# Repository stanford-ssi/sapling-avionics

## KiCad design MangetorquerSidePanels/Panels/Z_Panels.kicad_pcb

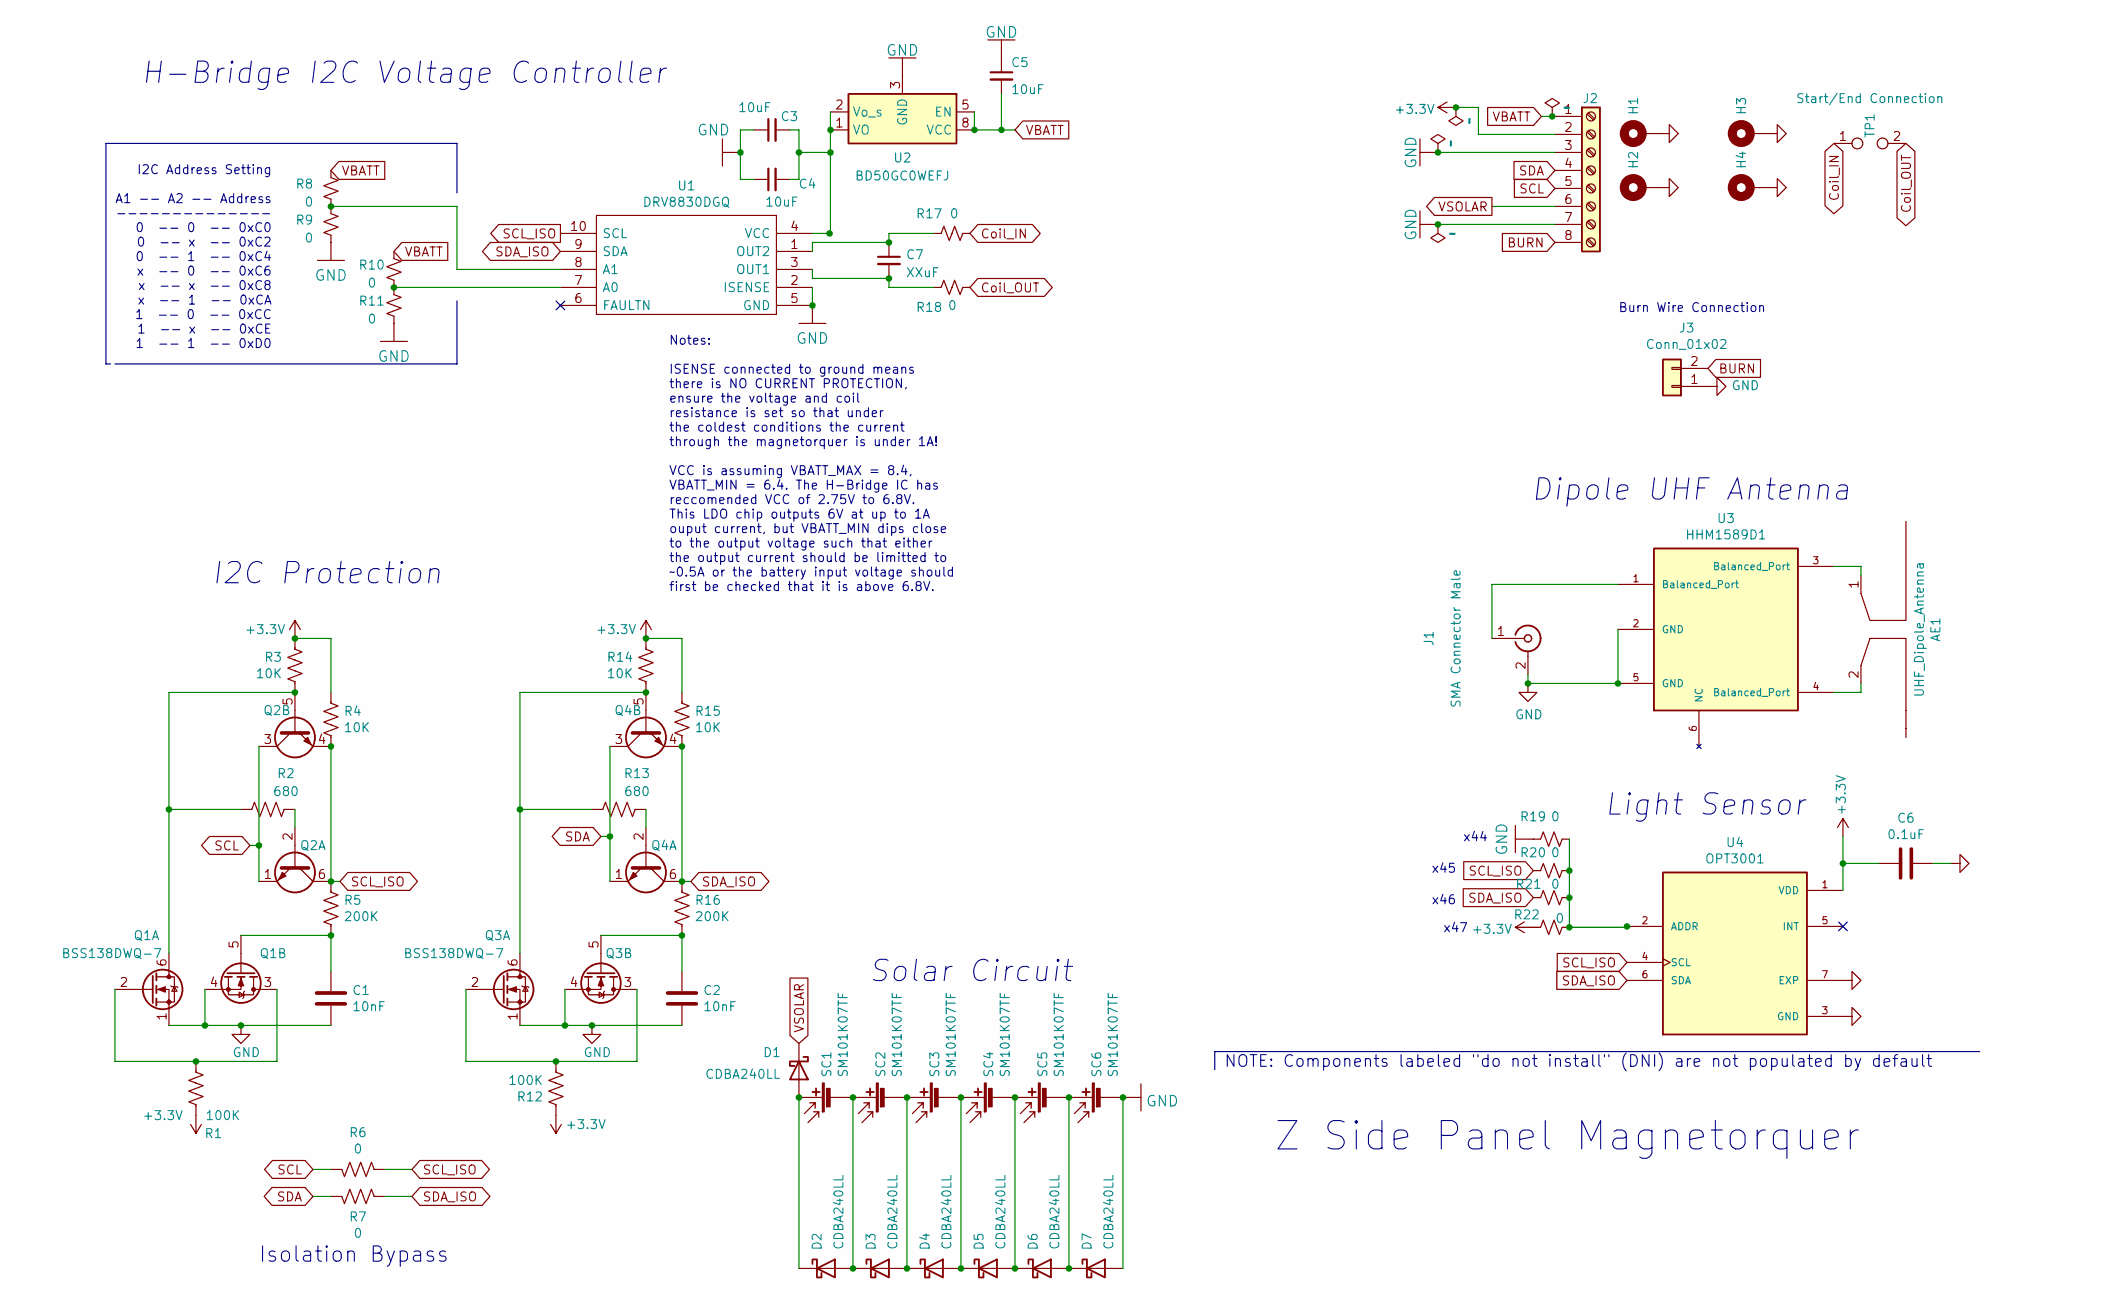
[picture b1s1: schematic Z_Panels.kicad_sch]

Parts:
AE1: UHF_Dipole_Antenna; UHF_Dipole_Antenna_Mount
C1, C2: 10nF; C_0603_1608Metric
C3, C4, C5: 10uF; C_1206_3216Metric
C6: 0.1uF; C_0603_1608Metric
C7: XXuF; C_1210_3225Metric
D1, D2, D3, D4, D5, D6, D7: CDBA240LL; DO-214AC
H1, H2, H3, H4: MountingHole_2.2mm_M2_DIN965_Pad_TopBottom
J1: SMA Connector Male; SMA_Amphenol_901-144_Vertical
J2: Screw_Terminal_01x08; PinHeader_1x08_P2.54mm_Vertical
J3: Conn_01x02; Burn_Wire_Connection
Q1, Q3: BSS138DWQ-7; Manufacturer_Part_Number BSS138DWQ-7; Mouser Part Number 621-BSS138DWQ-7
Q2, Q4: MBT2222ADW1T1; SOT-363_SC-70-6
R1, R12: 100K; R_0603_1608Metric
R2, R13: 680; R_0603_1608Metric
R3, R4, R14, R15: 10K; R_0603_1608Metric
R5, R16: 200K; R_0603_1608Metric
R6, R7, R8, R9, R10, R11, R17, R18, R19, R20, R21, R22: 0; R_0603_1608Metric
SC1, SC2, SC3, SC4, SC5, SC6: SM101K07TF
TP1: Start/End Connection; TestPointConnection
U1: DRV8830DGQ; Manufacturer_Part_Number DRV8830DGQR; Mouser Part Number 595-DRV8830DGQR
U2: BD50GC0WEFJ; HTSOP-8-1EP_3.9x4.9mm_P1.27mm_EP2.4x3.2mm
U3: HHM1589D1; Balun_Johanson_5400BL15B050E
U4: OPT3001

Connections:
+3V3: C6.1, J2.2, R1.2, R3.1, R4.2, R12.2, R14.1, R15.2, R22.1, U4.1 (VDD)
BURN: J2.8, J3.2
Coil_IN: R17.2, TP1.1
Coil_OUT: R18.2, TP1.2
unnamed: AE1.1, U3.3 (Balanced_Port)
unnamed: AE1.2, U3.4 (Balanced_Port)
unnamed: C3.2, C4.2, U1.4 (VCC), U2.1 (VO), U2.2 (Vo_s)
unnamed: D1.2 (A), D2.1 (K), SC1.1 (+)
unnamed: D2.2 (A), D3.1 (K), SC1.2 (-), SC2.1 (+)
unnamed: D3.2 (A), D4.1 (K), SC2.2 (-), SC3.1 (+)
unnamed: D4.2 (A), D5.1 (K), SC3.2 (-), SC4.1 (+)
unnamed: D5.2 (A), D6.1 (K), SC4.2 (-), SC5.1 (+)
unnamed: D6.2 (A), D7.1 (K), SC5.2 (-), SC6.1 (+)
unnamed: J1.1 (In), U3.1 (Balanced_Port)
unnamed: Q2.2 (B1), R2.2
unnamed: Q3.2 (G2), Q3.3 (D2), R12.1
unnamed: Q4.2 (B1), R13.1
unnamed: Q1.2 (G2), Q1.3 (D2), R1.1
unnamed: Q1.6 (D1), Q2.5 (B2), R2.1, R3.2
unnamed: C1.1, Q1.5 (G1), R5.1
unnamed: R8.2, R9.1, U1.8 (A1)
unnamed: R10.2, R11.1, U1.7 (A0)
unnamed: Q3.6 (D1), Q4.5 (B2), R13.2, R14.2
unnamed: C2.1, Q3.5 (G1), R16.1
unnamed: C7.1, R17.1, U1.1 (OUT2)
unnamed: C7.2, R18.1, U1.3 (OUT1)
unnamed: R19.2, R20.2, R21.2, R22.2, U4.2 (ADDR)
SCL: J2.5, Q2.1 (E1), Q2.3 (C2), R6.1
SCL_ISO: Q2.4 (E2), Q2.6 (C1), R4.1, R5.2, R6.2, R20.1, U1.10 (SCL), U4.4 (SCL)
SDA: J2.4, Q4.1 (E1), Q4.3 (C2), R7.1
SDA_ISO: Q4.4 (E2), Q4.6 (C1), R7.2, R15.1, R16.2, R21.1, U1.9 (SDA), U4.6 (SDA)
VBATT: C5.2, J2.1, R8.1, R10.1, U2.5 (EN), U2.8 (VCC)
VSOLAR: D1.1 (K), J2.6

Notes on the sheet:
Notes: ISENSE connected to ground means there is NO CURRENT PROTECTION, ensure the voltage and coil resistance is set so that under the coldest conditions the current through the magnetorquer is under 1A! VCC is assuming VBATT_MAX = 8.4, VBATT_MIN = 6.4. The H-Bridge IC has reccomended VCC of 2.75V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
x47
NOTE: Components labeled "do not install" (DNI) are not populated by default
Solar Circuit
x45
Z Side Panel Magnetorquer
Light Sensor
I2C Address Setting A1 -- A2 -- Address -------------- 0 -- 0 -- 0xC0 0 -- x -- 0xC2 0 -- 1 -- 0xC4 x -- 0 -- 0xC6 x -- x -- 0xC8 x -- 1 -- 0xCA 1 -- 0 -- 0xCC 1 -- x -- 0xCE 1 -- 1 -- 0xD0
H-Bridge I2C Voltage Controller
Burn Wire Connection
Dipole UHF Antenna
x44
Isolation Bypass
x46
I2C Protection

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
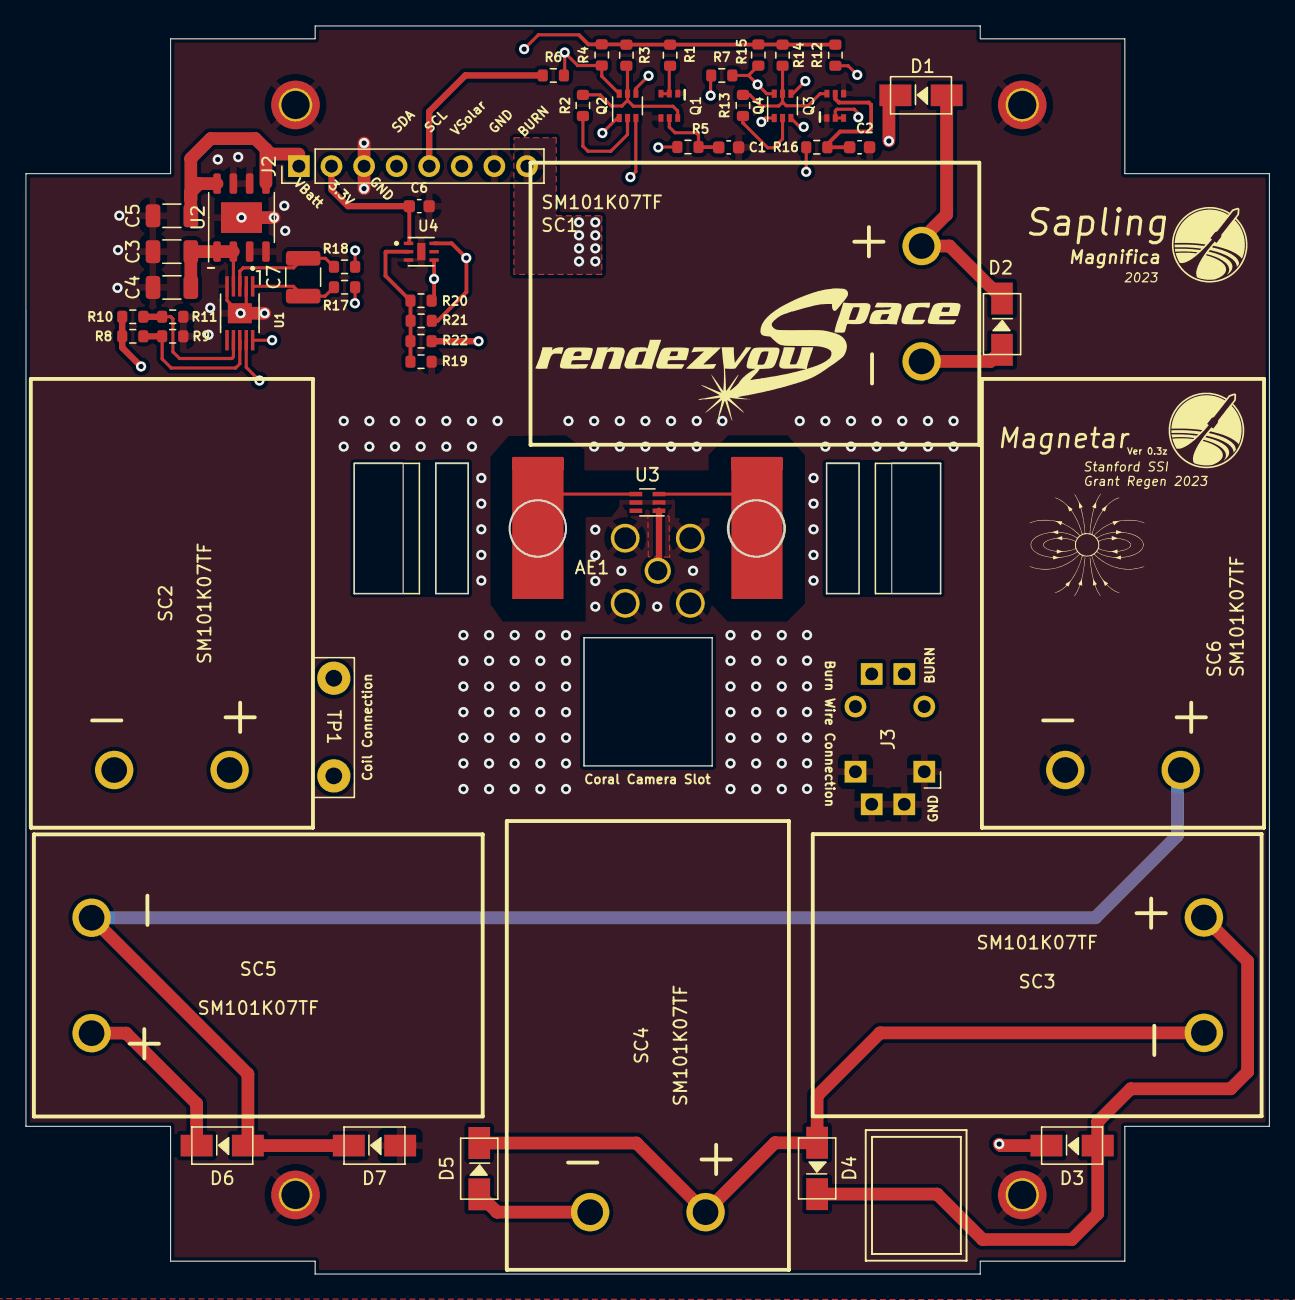
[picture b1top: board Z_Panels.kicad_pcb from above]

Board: 6 copper layers, 97.0 x 97.3 mm, 59 parts (1 on the bottom side), 34 nets.

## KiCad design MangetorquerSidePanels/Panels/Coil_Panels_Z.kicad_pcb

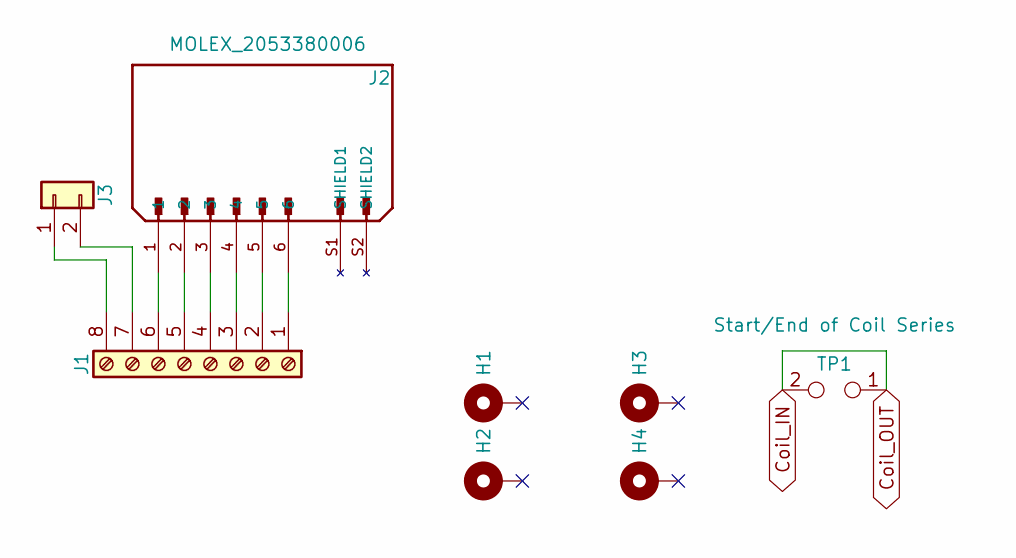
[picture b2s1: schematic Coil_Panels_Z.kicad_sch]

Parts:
H1, H2, H3, H4: MountingHole_2.2mm_M2_DIN965_Pad_TopBottom
J1: Screw_Terminal_01x08; PinHeader_1x08_P2.54mm_Vertical
J2: MOLEX_2053380006
J3: Conn_01x02; 2053380002
TP1: Start/End of Coil Series; TestPointConnection

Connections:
Coil_IN: TP1.1, TP1.2
unnamed: J1.7, J3.2
unnamed: J1.6, J2.1
unnamed: J1.5, J2.2
unnamed: J1.4, J2.3
unnamed: J1.3, J2.4
unnamed: J1.2, J2.5
unnamed: J1.1, J2.6
unnamed: J1.8, J3.1

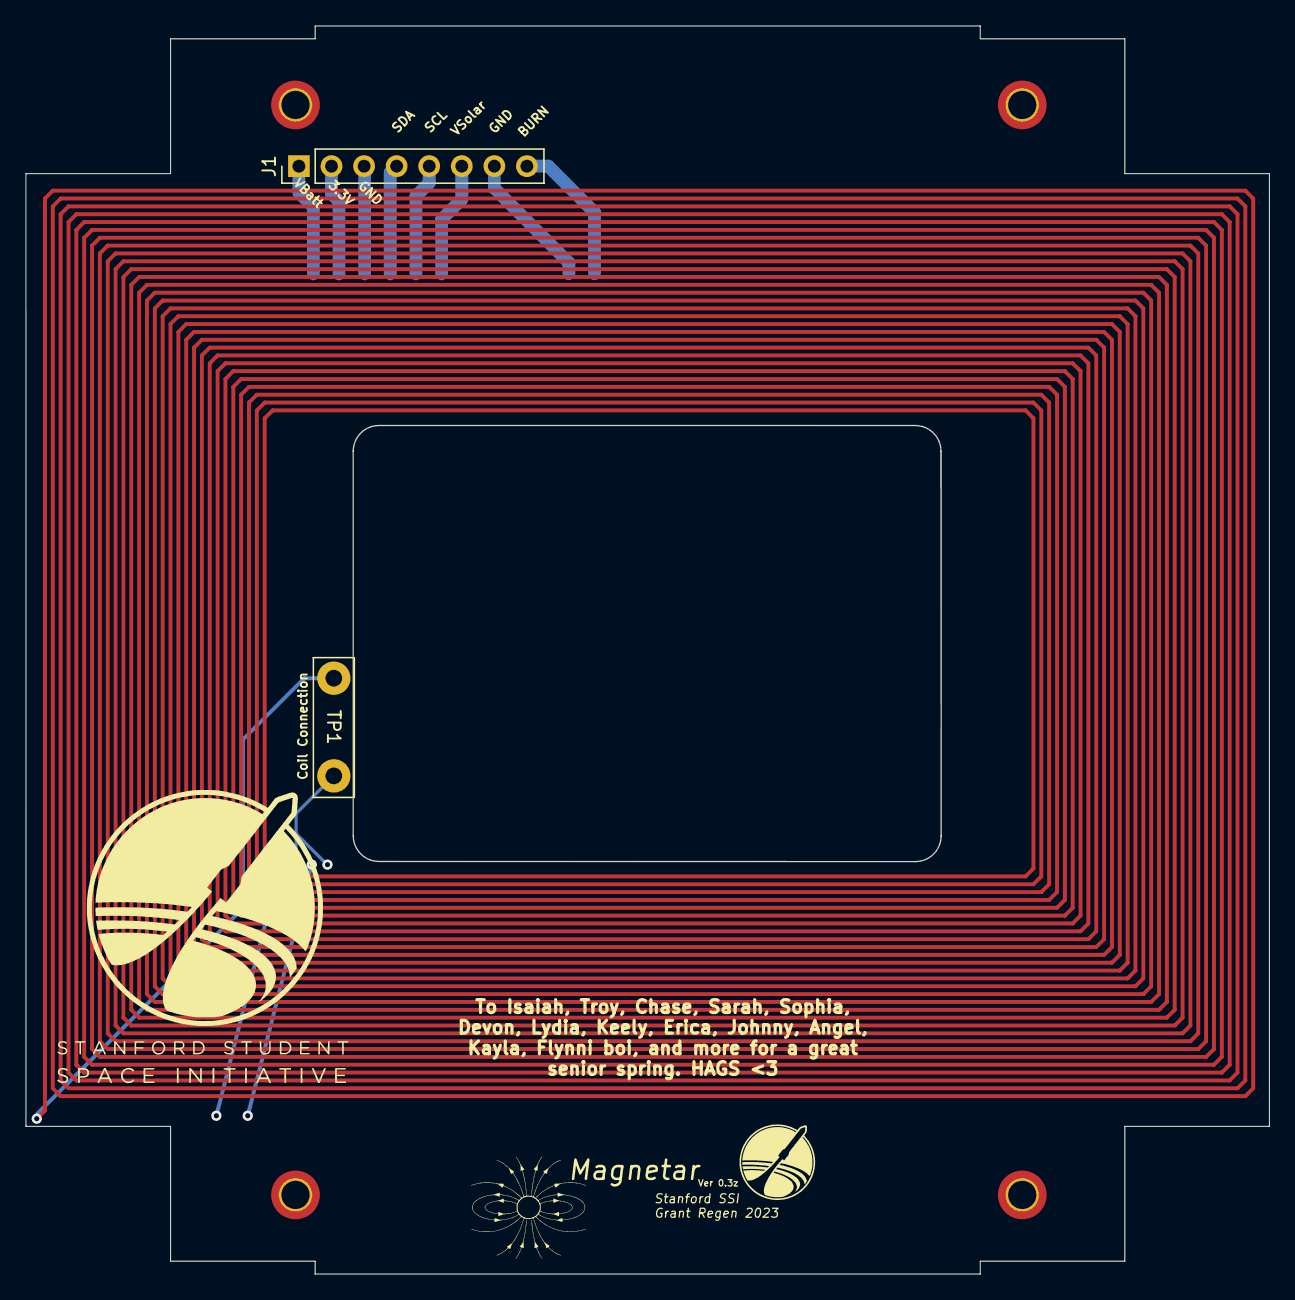
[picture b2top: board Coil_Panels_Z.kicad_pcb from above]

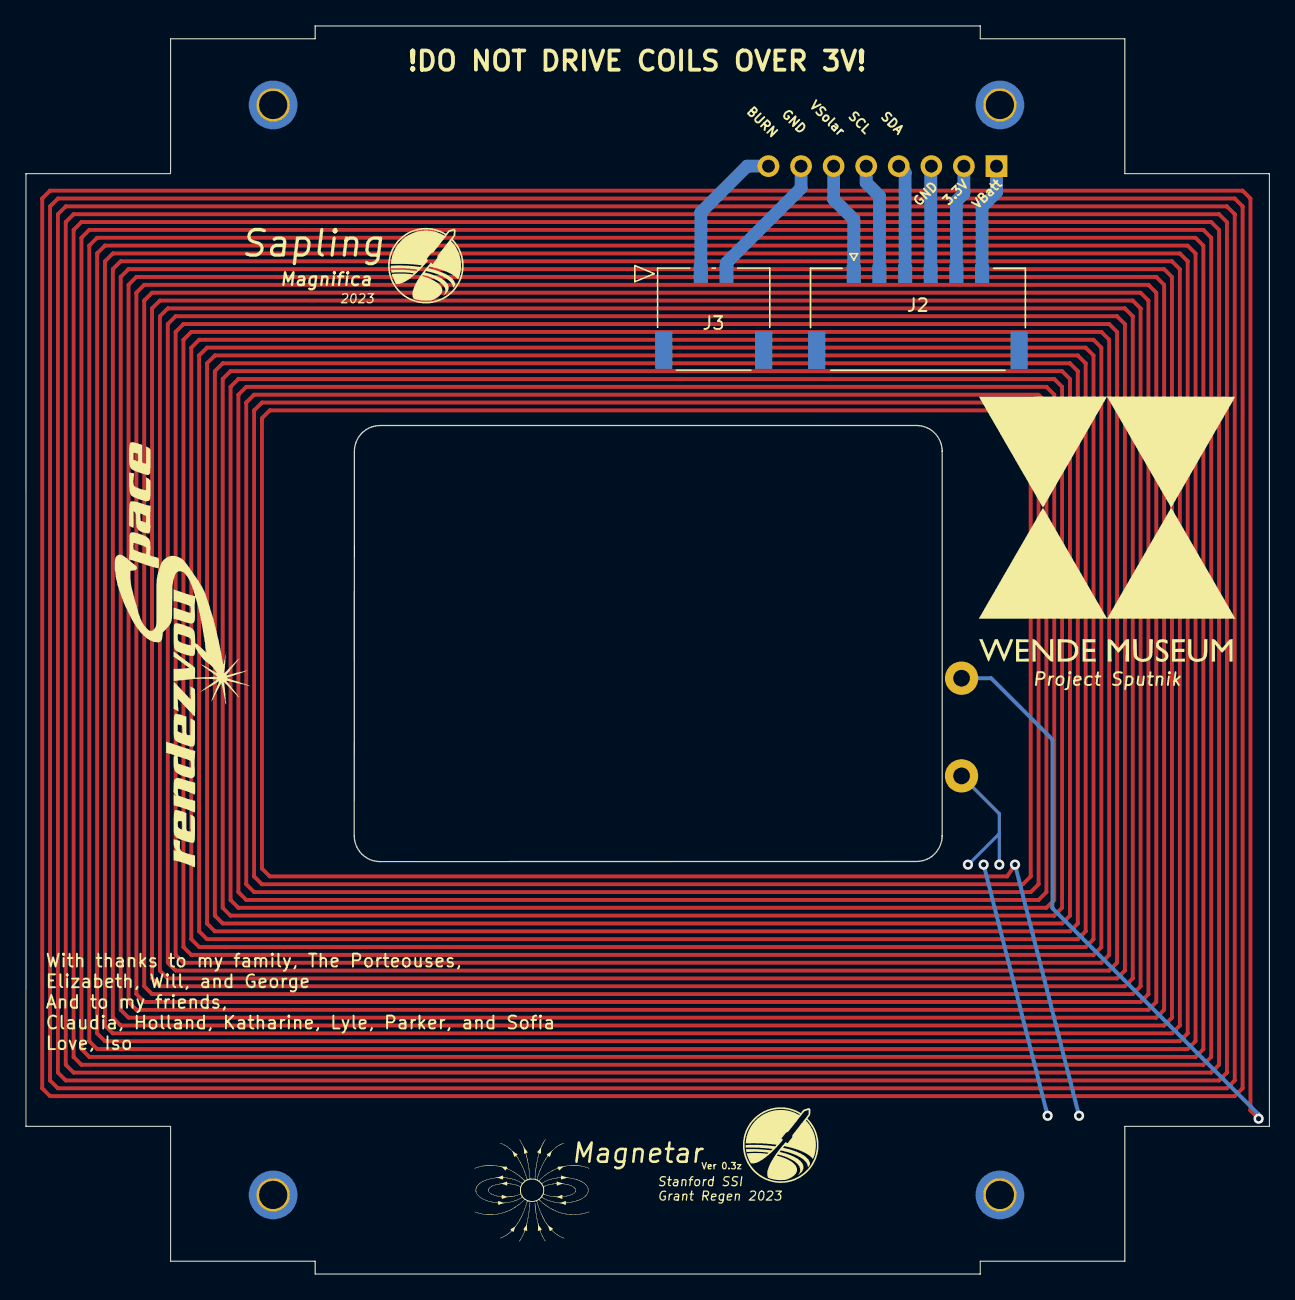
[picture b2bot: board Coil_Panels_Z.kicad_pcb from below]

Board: 6 copper layers, 97.0 x 97.3 mm, 8 parts (2 on the bottom side), 9 nets.

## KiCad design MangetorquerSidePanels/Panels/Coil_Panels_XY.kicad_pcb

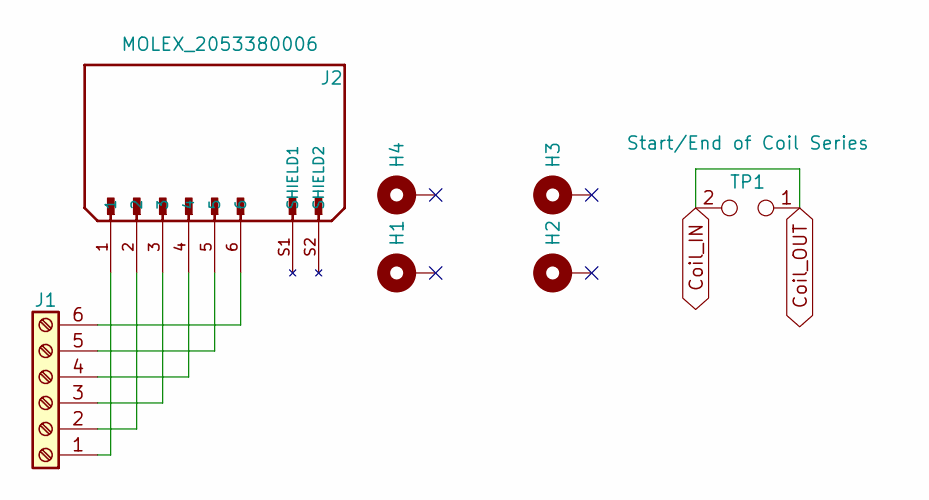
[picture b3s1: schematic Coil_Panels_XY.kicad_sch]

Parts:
H1, H2, H3, H4: MountingHole_2.2mm_M2_DIN965_Pad_TopBottom
J1: Through_Hole_1; PinHeader_1x06_P2.54mm_Vertical
J2: MOLEX_2053380006
TP1: Start/End of Coil Series; TestPointConnection

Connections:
Coil_IN: TP1.1, TP1.2
unnamed: J1.1, J2.1
unnamed: J1.2, J2.2
unnamed: J1.3, J2.3
unnamed: J1.4, J2.4
unnamed: J1.5, J2.5
unnamed: J1.6, J2.6

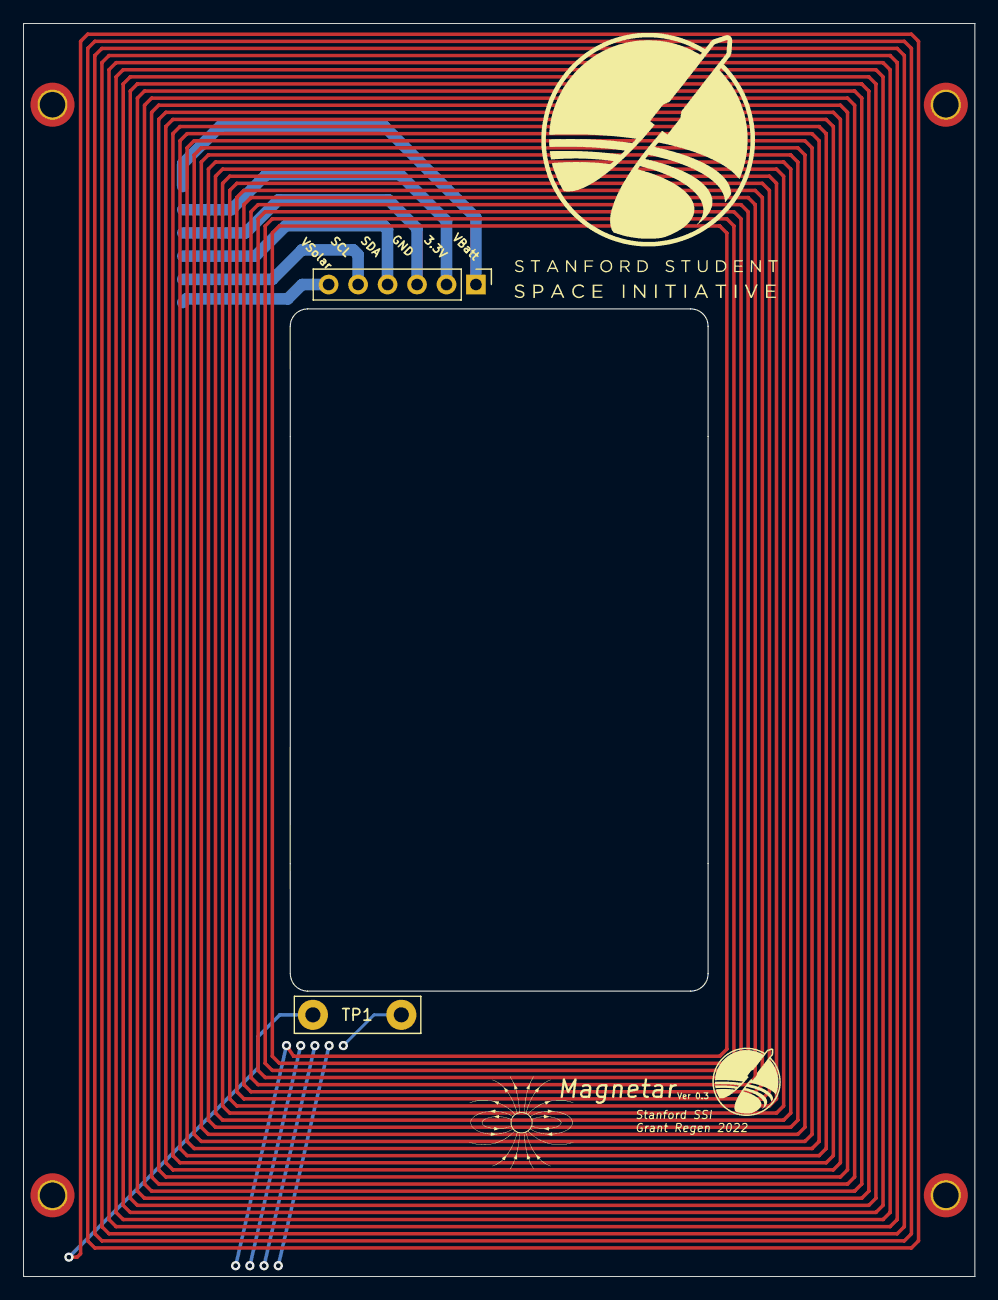
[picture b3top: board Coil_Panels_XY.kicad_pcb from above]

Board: 6 copper layers, 82.0 x 108.0 mm, 7 parts (1 on the bottom side), 7 nets.

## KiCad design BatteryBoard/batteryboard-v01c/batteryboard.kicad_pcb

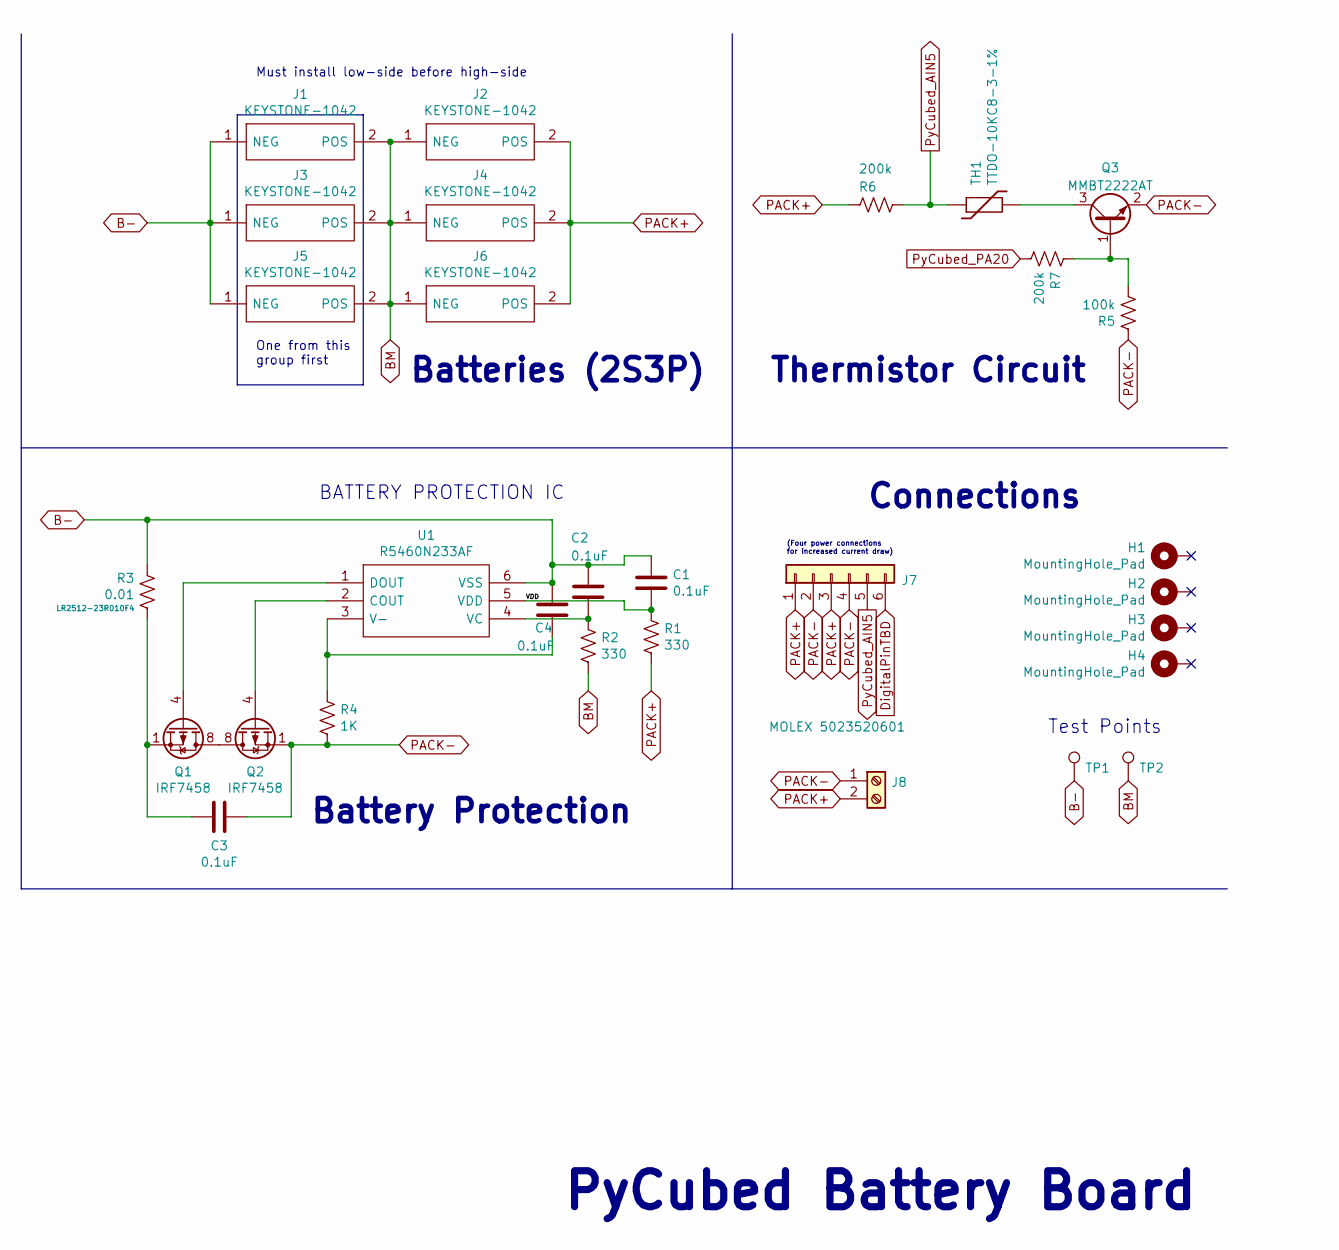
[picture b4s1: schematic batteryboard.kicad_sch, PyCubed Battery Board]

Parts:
C1, C2, C3, C4: 0.1uF; C_0603_1608Metric
H1, H2, H3, H4: MountingHole_Pad; MountingHole_3.2mm_M3_DIN965_PadMOD
J1, J2, J3, J4, J5, J6: KEYSTONE-1042; Keystone_1042; Manufacturer_Part_Number 1042; Mouser Part Number 534-1042
J7: MOLEX 5023520601; 5023520600
J8: Screw_Terminal_01x02; pheonix_2pos_screwterminal
Q1, Q2: IRF7458; SOIC-8_3.9x4.9mm_P1.27mm
Q3: MMBT2222AT; SOT-23
R1, R2: 330; R_0603_1608Metric
R3: 0.01; R_2512_6332Metric
R4: 1K; R_0603_1608Metric; Manufacturer_Part_Number LR2512-23R010F4
R5: 100k; R_0603_1608Metric
R6: 200k; R_1206_3216Metric
R7: 200k; R_0603_1608Metric
TH1: TTDO-10KC8-3-1%; R_Axial_DIN0204_L3.6mm_D1.6mm_P5.08mm_Horizontal
TP1, TP2: TestPoint; TestPoint_Loop_D1.80mm_Drill1.0mm_Beaded
U1: R5460N233AF; SOT95P280X130-6N; Manufacturer_Part_Number R5460N233AF-TR-FE; Mouser Part Number 848-R5460N233AFTRFE

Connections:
/VDD: C1.2, R1.2, U1.5 (VDD)
B-: C1.1, C2.1, C4.1, J1.1 (NEG), J3.1 (NEG), J5.1 (NEG), R3.1, TP1.1, U1.6 (VSS)
BM: J1.2 (POS), J2.1 (NEG), J3.2 (POS), J4.1 (NEG), J5.2 (POS), J6.1 (NEG), R2.1, TP2.1
DigitalPinTBD: J7.6
unnamed: C2.2, R2.2, U1.4 (VC)
unnamed: C3.1, Q1.1 (S), Q1.2 (S), Q1.3 (S), R3.2
unnamed: C4.2, R4.1, U1.3 (V-)
unnamed: Q1.4 (G), U1.1 (DOUT)
unnamed: Q1.5 (D), Q1.6 (D), Q1.7 (D), Q1.8 (D), Q2.5 (D), Q2.6 (D), Q2.7 (D), Q2.8 (D)
unnamed: Q2.4 (G), U1.2 (COUT)
unnamed: Q3.1 (B), R5.1, R7.2
unnamed: Q3.3 (C), TH1.2
PACK+: J2.2 (POS), J4.2 (POS), J6.2 (POS), J7.1, J7.3, J8.2, R1.1, R6.1
PACK-: C3.2, J7.2, J7.4, J8.1, Q2.1 (S), Q2.2 (S), Q2.3 (S), Q3.2 (E), R4.2, R5.2
PyCubed_AIN5: J7.5, R6.2, TH1.1
PyCubed_PA20: R7.1

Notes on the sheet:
Connections
(Four power connections for increased current draw)
One from this group first
PyCubed Battery Board
Batteries (2S3P)
Test Points
Battery Protection
Must install low-side before high-side
Thermistor Circuit
BATTERY PROTECTION IC

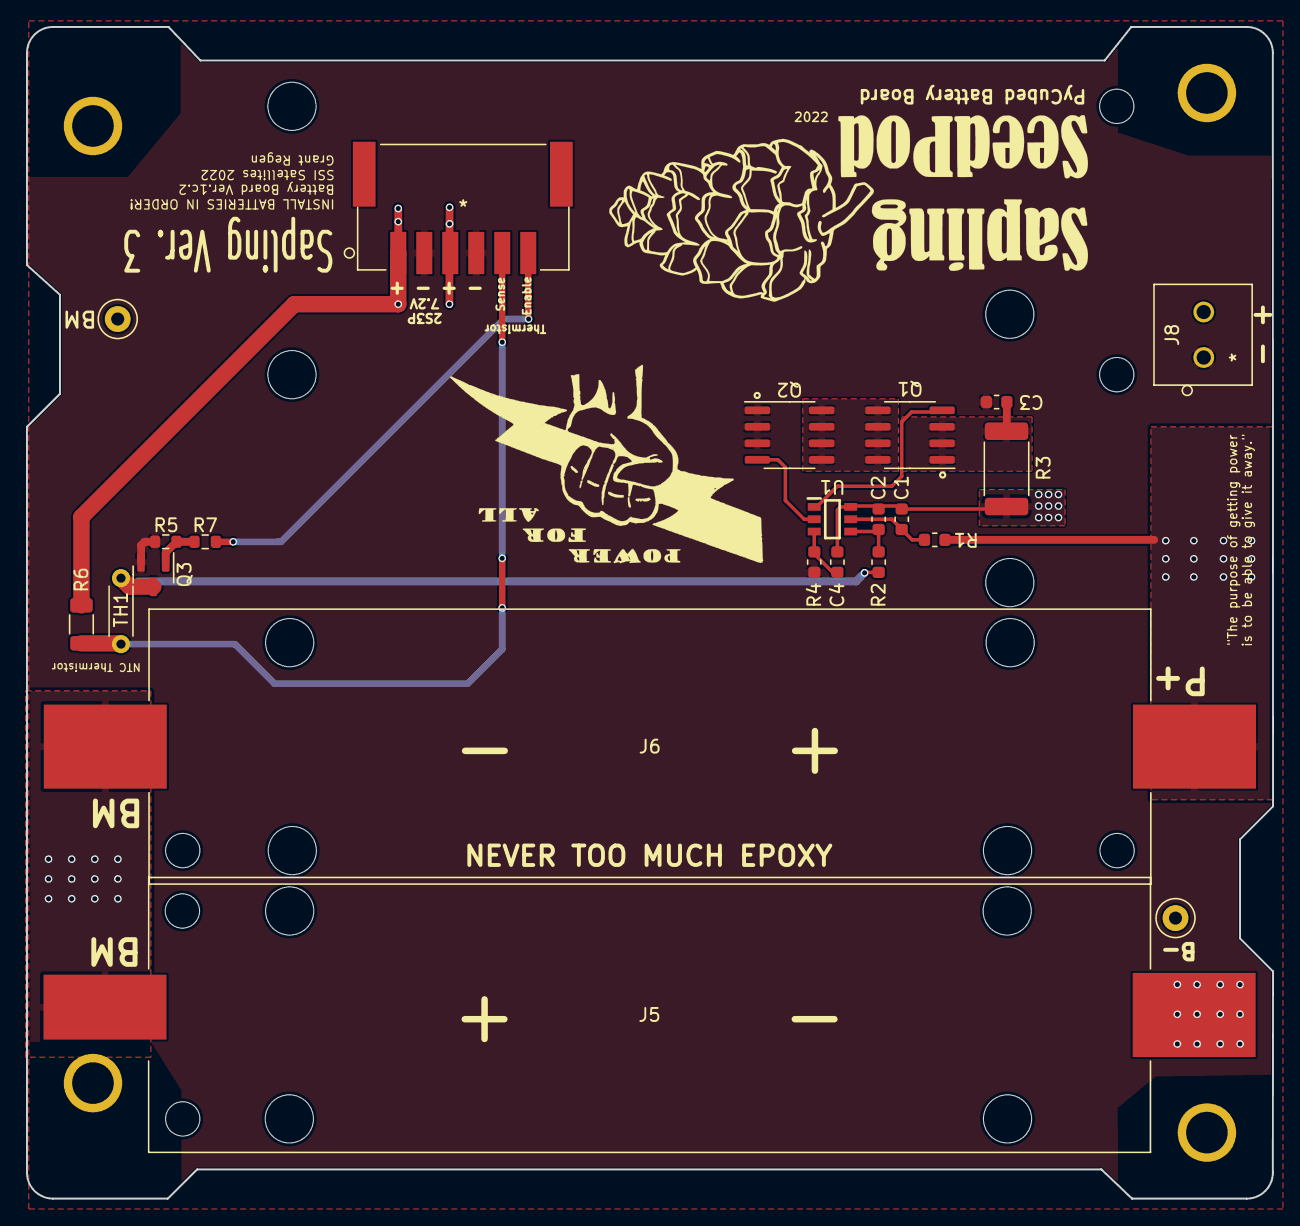
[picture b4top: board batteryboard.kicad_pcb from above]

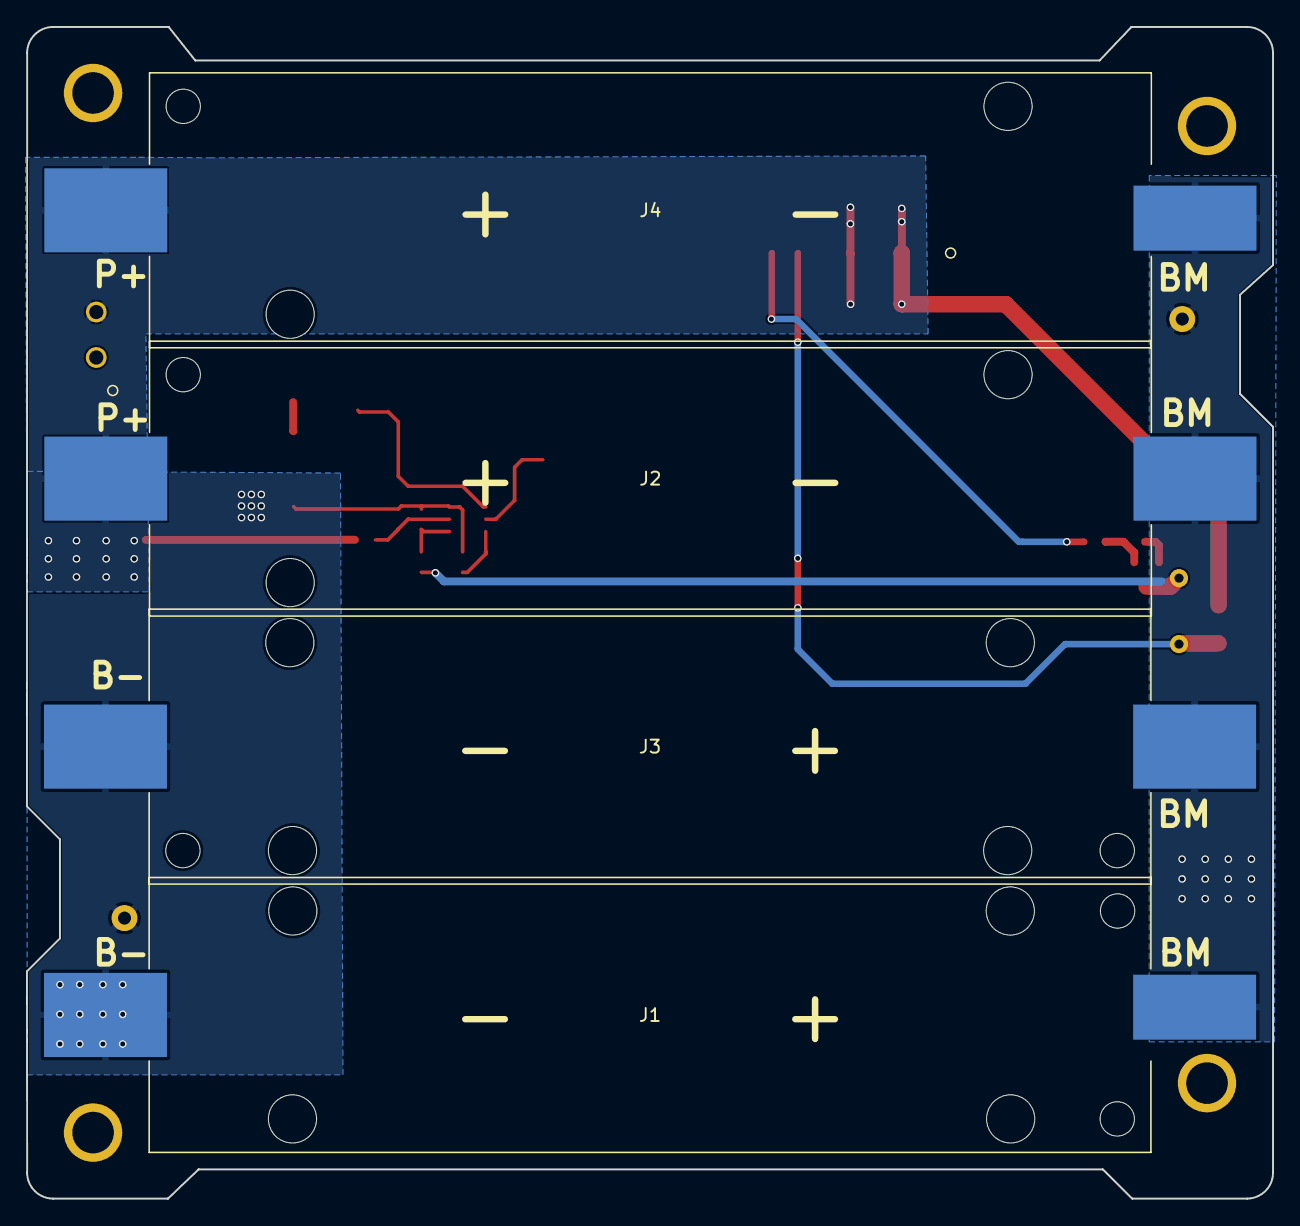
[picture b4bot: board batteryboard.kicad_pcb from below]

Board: 2 copper layers, 95.9 x 90.2 mm, 32 parts (4 on the bottom side), 14 nets.

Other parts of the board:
Ref**: Val**; SeedPodLogo
Ref**#2: Val**; PowerLogo

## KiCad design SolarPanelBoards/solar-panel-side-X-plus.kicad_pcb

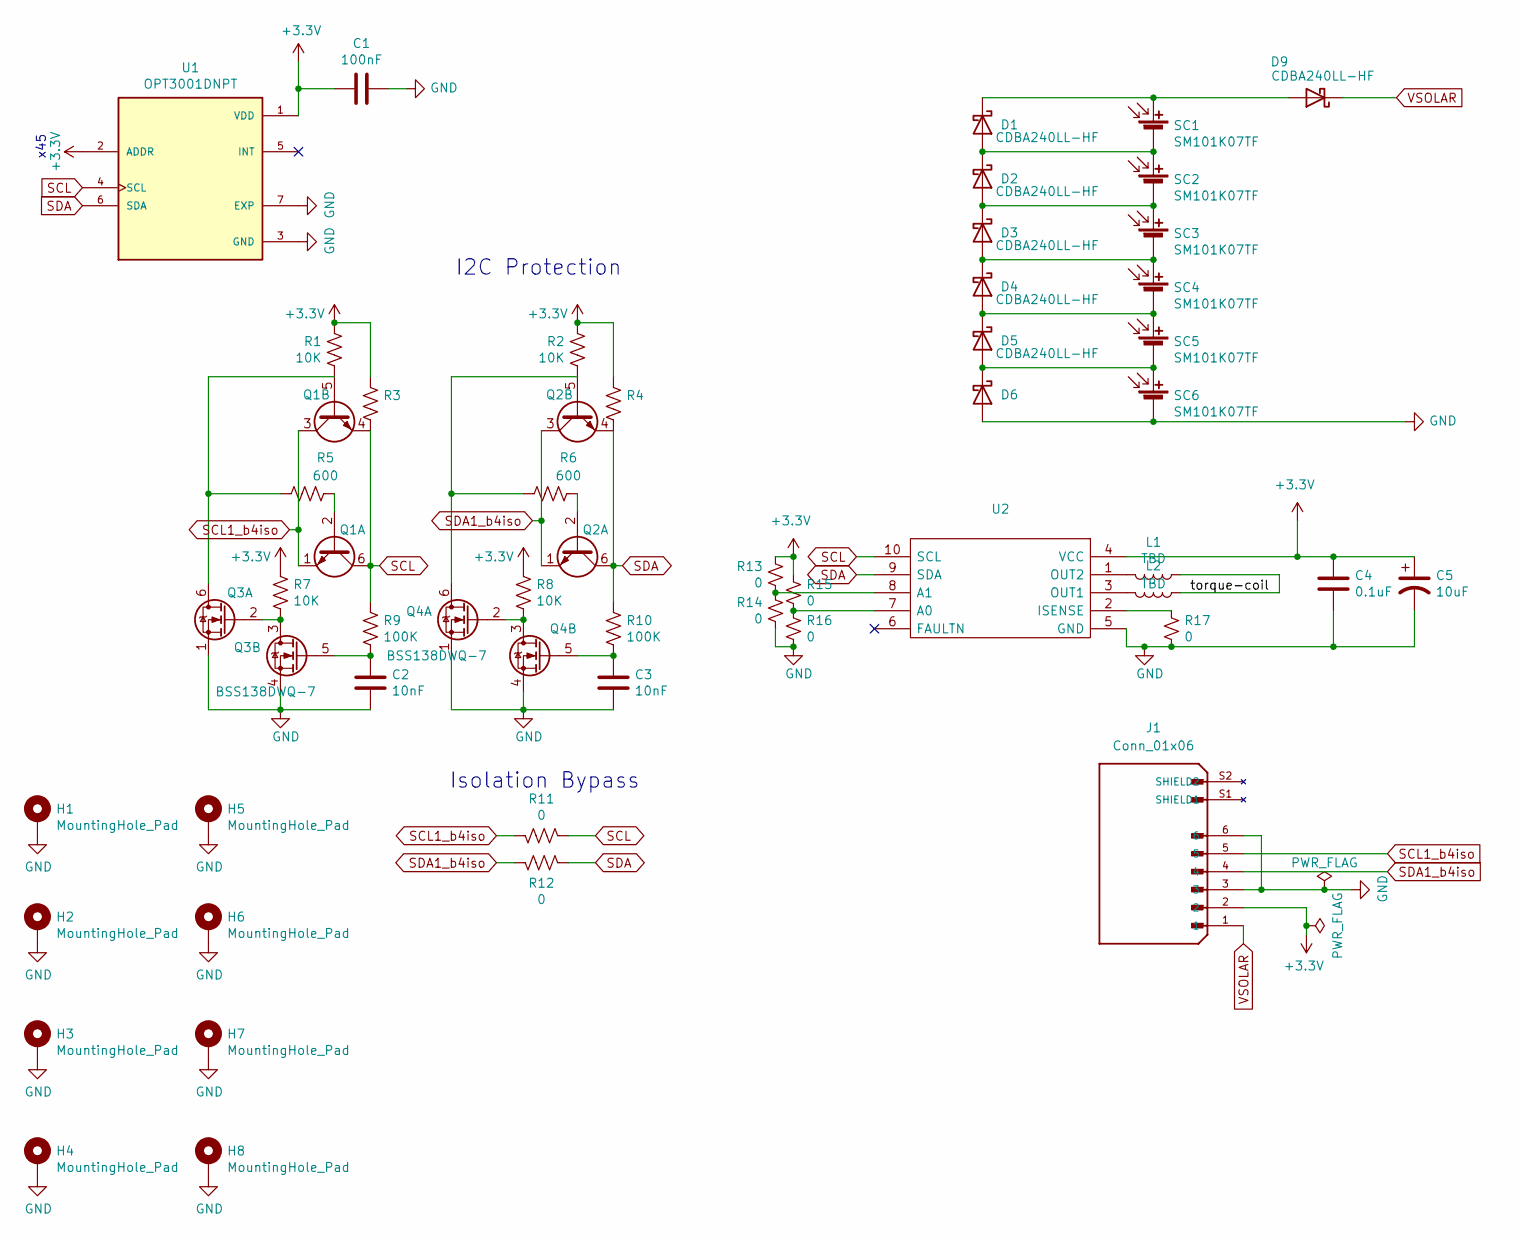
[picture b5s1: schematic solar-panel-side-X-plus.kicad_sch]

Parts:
C1: 100nF; C_0603_1608Metric
C2, C3: 10nF; C_0603_1608Metric
C4: 0.1uF; C_0402_1005Metric
C5: 10uF; C_0805_2012Metric
D1, D2, D3, D4, D5, D9: CDBA240LL-HF; DO-214AC
D6: (no value)
H1, H2, H3, H4, H5, H6, H7, H8: MountingHole_Pad; MountingHole_2.2mm_M2_DIN965_Pad_TopBottom
J1: Conn_01x06; MOLEX_2053380006
L1, L2: TBD; L_0603_1608Metric
Q1, Q2: MBT2222ADW1T1; SOT-363_SC-70-6
Q3, Q4: BSS138DWQ-7; Manufacturer_Part_Number BSS138DWQ-7; Mouser Part Number 621-BSS138DWQ-7
R1, R2, R7, R8: 10K; R_0603_1608Metric
R3, R4: (no value)
R5, R6: 600; R_0603_1608Metric
R9, R10: 100K; R_0603_1608Metric
R11, R12: 0; R_0603_1608Metric
R13, R14, R15, R16, R17: 0; R_0402_1005Metric
SC1, SC2, SC3, SC4, SC5, SC6: SM101K07TF
U1: OPT3001DNPT; OPT3001
U2: Manufacturer_Part_Number DRV8830DGQR; Mouser Part Number 595-DRV8830DGQR

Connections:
+3V3: C1.1, C4.1, C5.1, J1.2, R1.1, R2.1, R3.2, R4.2, R7.2, R8.2, R13.2, R15.2, U1.1 (VDD), U1.2 (ADDR), U2.4 (VCC)
/torque-coil: L1.1, L2.1
GND: C1.2, C2.2, C3.2, C4.2, C5.2, D6.2 (A), H1.1, H2.1, H3.1, H4.1, H5.1, H6.1, H7.1, H8.1, J1.3, J1.6, Q3.1 (S2), Q3.4 (S1), Q4.1 (S2), Q4.4 (S1), R14.1, R16.1, R17.1, SC6.2 (-), U1.3 (GND), U1.7 (EXP), U2.5 (GND), U2.EPAD
unnamed: C2.1, Q3.5 (G1), R9.1
unnamed: C3.1, Q4.5 (G1), R10.1
unnamed: D1.1 (K), D9.2 (A), SC1.1 (+)
unnamed: D1.2 (A), D2.1 (K), SC1.2 (-), SC2.1 (+)
unnamed: D2.2 (A), D3.1 (K), SC2.2 (-), SC3.1 (+)
unnamed: D3.2 (A), D4.1 (K), SC3.2 (-), SC4.1 (+)
unnamed: D4.2 (A), D5.1 (K), SC4.2 (-), SC5.1 (+)
unnamed: D5.2 (A), D6.1 (K), SC5.2 (-), SC6.1 (+)
unnamed: L1.2, U2.1 (OUT2)
unnamed: L2.2, U2.3 (OUT1)
unnamed: Q1.2 (B1), R5.2
unnamed: Q1.5 (B2), Q3.6 (D1), R1.2, R5.1
unnamed: Q2.2 (B1), R6.1
unnamed: Q2.5 (B2), Q4.6 (D1), R2.2, R6.2
unnamed: Q3.2 (G2), Q3.3 (D2), R7.1
unnamed: Q4.2 (G2), Q4.3 (D2), R8.1
unnamed: R13.1, R14.2, U2.8 (A1)
unnamed: R15.1, R16.2, U2.7 (A0)
unnamed: R17.2, U2.2 (ISENSE)
SCL: Q1.4 (E2), Q1.6 (C1), R3.1, R9.2, R11.2, U1.4 (SCL), U2.10 (SCL)
SCL1_b4iso: J1.5, Q1.1 (E1), Q1.3 (C2), R11.1
SDA: Q2.4 (E2), Q2.6 (C1), R4.1, R10.2, R12.2, U1.6 (SDA), U2.9 (SDA)
SDA1_b4iso: J1.4, Q2.1 (E1), Q2.3 (C2), R12.1
VSOLAR: D9.1 (K), J1.1

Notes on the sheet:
x45
Isolation Bypass
I2C Protection

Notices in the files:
parts and their libraries:
Copyright 2021 Accelerated Designs. All rights reserved.
Copyright 2016 Accelerated Designs. All rights reserved.
